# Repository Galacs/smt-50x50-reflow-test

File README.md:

# SMT 50x50 reflow test

ESP32-C6 50x50 board made to test smd reflow techniques with various components packages (QFN, HTSOP, WSON, USBC, SOT, SOIC, 0201)

## IC List

- ESP32-C6 (Main MCU)
- W25Q128JVSIQ (16MB program storage spi flash)
- 2x TMP117 (I2C temperature sensor)
- BMP581 (I2C/SPI pressure sensor)
- LMR36520 (wide Vin buck converter)
- LM317A (high Vin LDO)
- AP2112K (MCU LDO)
- 2450AT18A100E (2.45GHz Ceramic chip antenna)
- 01005 resistors

## Top preview

## Preview 3d render

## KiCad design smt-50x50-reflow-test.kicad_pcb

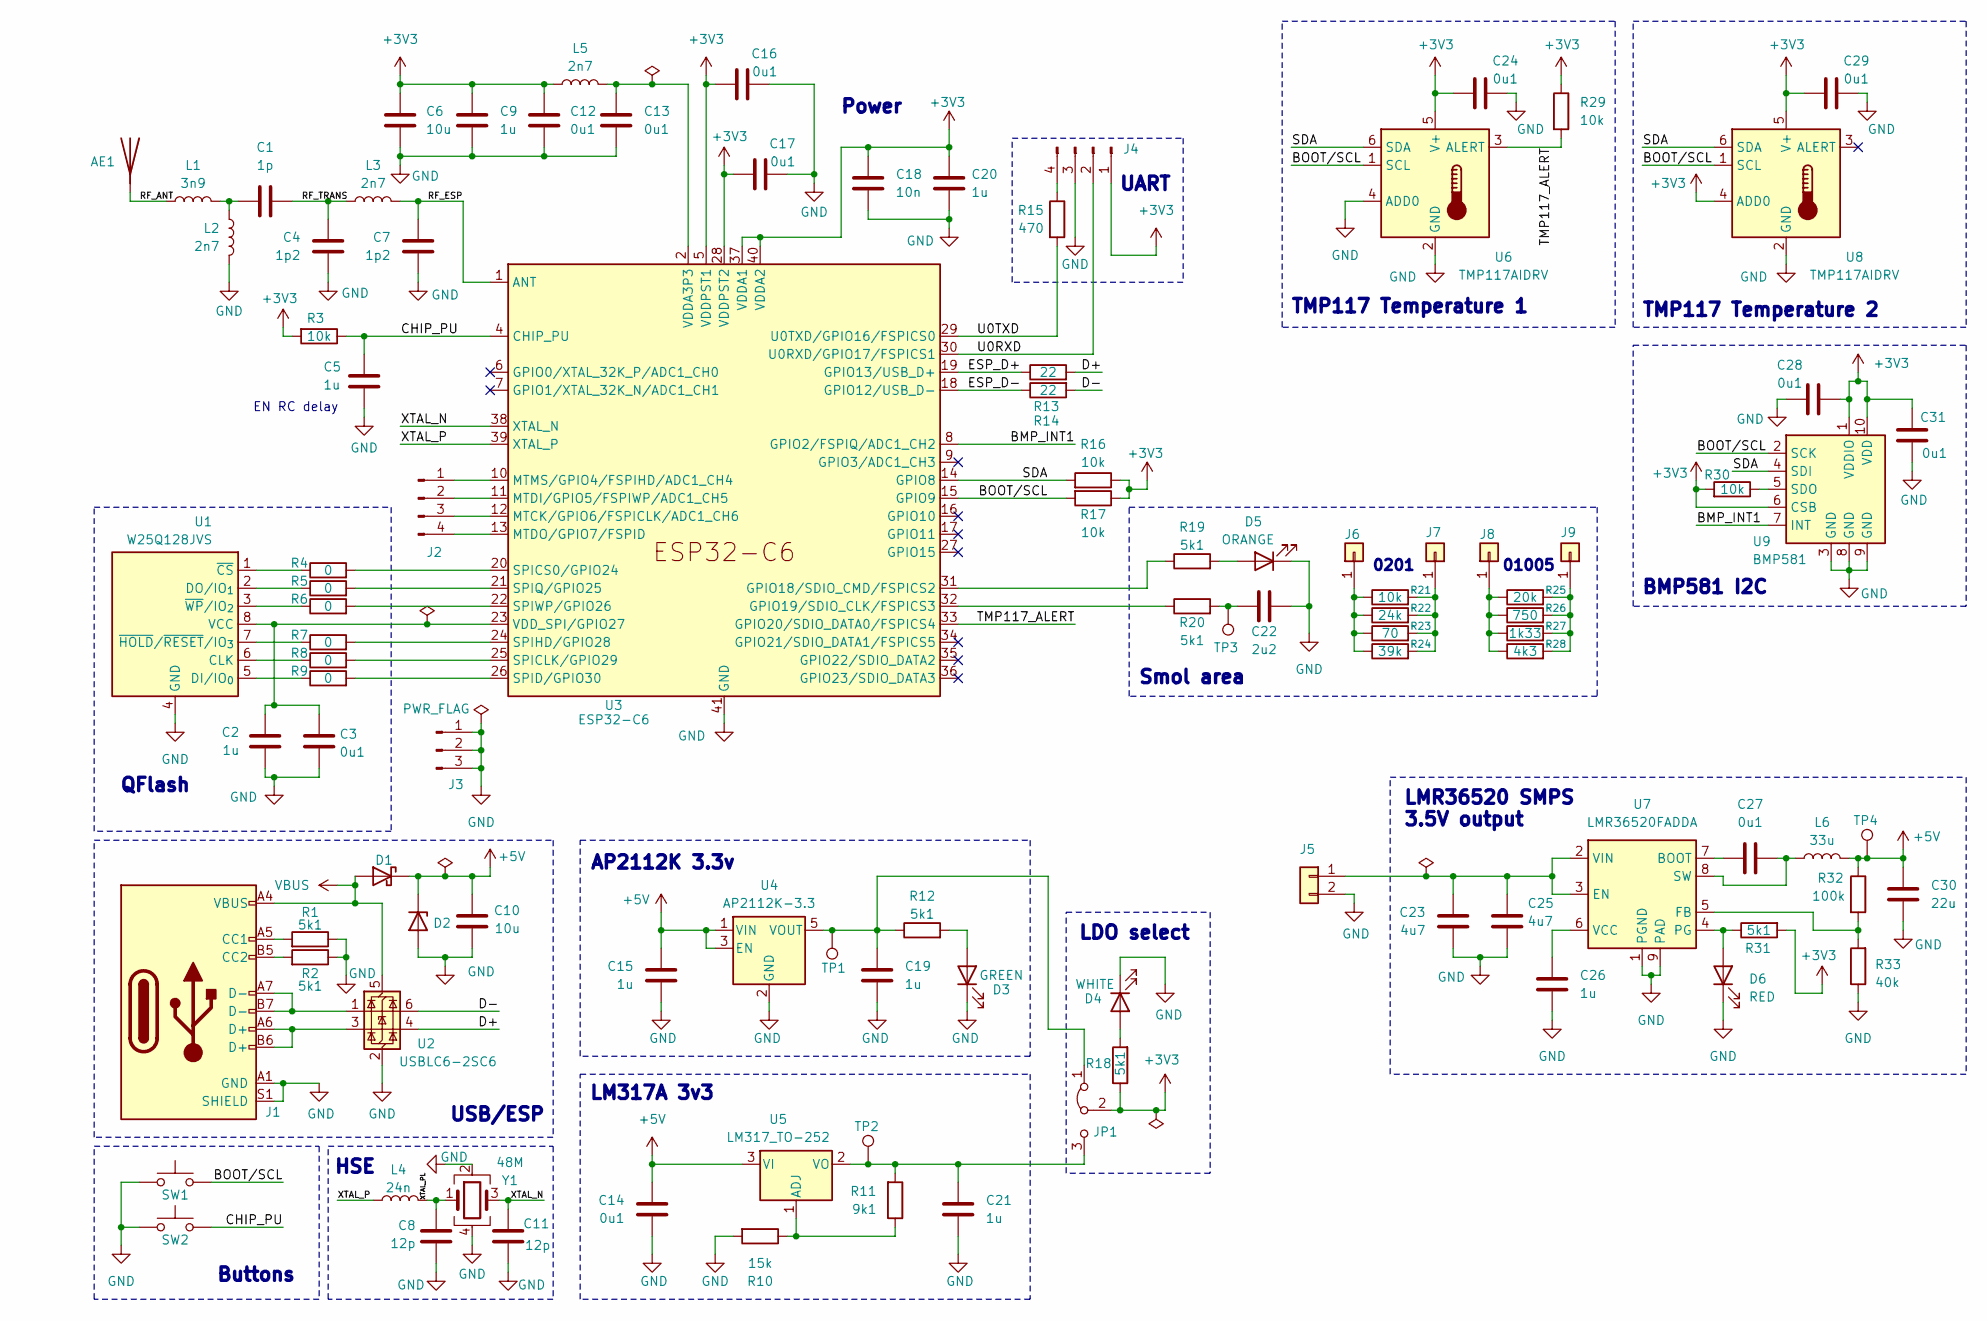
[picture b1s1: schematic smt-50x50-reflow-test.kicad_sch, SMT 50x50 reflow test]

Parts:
AE1: Antenna; Johanson_2450AT18x100; Manufacturer Part Number 2450AT18A100E; JLCPCB Part # C89334
C1: 1p; C_0402_1005Metric; Manufacturer Part Number 0402CG1R0C500NT; JLCPCB Part # C1550
C2, C5, C9, C20, C26: 1u; C_0402_1005Metric; Manufacturer Part Number CL05A105KA5NQNC; JLCPCB Part # C52923
C3, C12, C13, C16, C17, C24, C27, C28, C29, C31: 0u1; C_0402_1005Metric; Manufacturer Part Number CL05B104KB54PNC; JLCPCB Part # C307331
C4, C7: 1p2; C_0402_1005Metric; Manufacturer Part Number GJM1555C1H1R2WB01D; JLCPCB Part # C76899
C6, C10: 10u; C_0402_1005Metric; Manufacturer Part Number CL05A106MQ5NUNC; JLCPCB Part # C15525
C8, C11: 12p; C_0402_1005Metric; Manufacturer Part Number 0402CG120J500NT; JLCPCB Part # C1547
C14: 0u1; C_0603_1608Metric; Manufacturer Part Number CC0603KRX7R9BB104; JLCPCB Part # C14663
C15, C19, C21: 1u; C_0603_1608Metric; Manufacturer Part Number CL10A105KB8NNNC; JLCPCB Part # C15849
C18: 10n; C_0402_1005Metric; Manufacturer Part Number CL05B103KB5NNNC; JLCPCB Part # C15195
C22: 2u2; C_0201_0603Metric; Manufacturer Part Number GRM033R61A225KE47D; JLCPCB Part # C335106
C23, C25: 4u7; C_1206_3216Metric; Manufacturer Part Number 1206B475K500NT; JLCPCB Part # C29823
C30: 22u; C_0603_1608Metric; Manufacturer Part Number CL10A226MQ8NRNC; JLCPCB Part # C59461
D1: D_Schottky; D_SMA; Manufacturer Part Number SS54; JLCPCB Part # C22452
D2: H5VU10U; Diode_DFN1006; Manufacturer Part Number H5VU10U; JLCPCB Part # C22395519
D3: GREEN; LED_0805_2012Metric; Manufacturer Part Number KT-0805G; JLCPCB Part # C2297
D4: WHITE; LED_0603_1608Metric; Manufacturer Part Number KT-0603W; JLCPCB Part # C2290
D5: ORANGE; LED_0201_0603Metric; Manufacturer Part Number XL-0201UOC; JLCPCB Part # C5440629
D6: RED; LED_0603_1608Metric; Manufacturer Part Number KT-0603R; JLCPCB Part # C2286
J1: USB_C_Receptacle_USB2.0_14P; USB_C_Receptacle_HRO_TYPE-C-31-M-12; Manufacturer Part Number TYPE-C16PIN; JLCPCB Part # C393939
J2, J4: Conn_01x04_Pin; PinHeader_1x04_P2.54mm_Vertical
J3: Conn_01x03_Pin; PinHeader_1x03_P2.54mm_Vertical
J5: Conn_01x02; PinHeader_1x02_P2.54mm_Vertical
J6, J7, J8, J9: Conn_01x01; TestPoint_Pad_D1.0mm
JP1: Jumper_3_Bridged12; PinHeader_1x03_P2.54mm_Vertical
L1: 3n9; L_0402_1005Metric; Manufacturer Part Number LQG15HS3N9S02D; JLCPCB Part # C77109
L2, L3, L5: 2n7; L_0402_1005Metric; Manufacturer Part Number LQG15HS2N7S02D; JLCPCB Part # C77108
L4: 24n; L_0402_1005Metric; Manufacturer Part Number LQW15AN24NG00D; JLCPCB Part # C167472
L6: 33u; L_Chilisin_BMRx00060630; Manufacturer Part Number FXL0630-330-M; JLCPCB Part # C177245
R1, R2, R12, R18, R31: 5k1; R_0603_1608Metric; Manufacturer Part Number 0603WAF5101T5E; JLCPCB Part # C23186
R3, R29, R30: 10k; R_0603_1608Metric; Manufacturer Part Number 0603WAF1002T5E; JLCPCB Part # C25804
R4, R5, R6, R7, R8, R9: 0; R_0402_1005Metric; Manufacturer Part Number 0402WGF0000TCE; JLCPCB Part # C17168
R10: 15k; R_0603_1608Metric; Manufacturer Part Number 0603WAF1502T5E; JLCPCB Part # C22809
R11: 9k1; R_0603_1608Metric; Manufacturer Part Number 0603WAF9101T5E; JLCPCB Part # C23260
R13, R14: 22; R_0402_1005Metric; Manufacturer Part Number 0402WGF220JTCE; JLCPCB Part # C25092
R15: 470; R_0402_1005Metric; Manufacturer Part Number 0402WGF4700TCE; JLCPCB Part # C25117
R16, R17: 10k; R_0402_1005Metric; Manufacturer Part Number 0402WGF1002TCE; JLCPCB Part # C25744
R19, R20: 5k1; R_0201_0603Metric; Manufacturer Part Number 0201WMF5101TEE; JLCPCB Part # C270344
R21: 10k; R_0201_0603Metric; Manufacturer Part Number 0201WMF1002TEE C473048; JLCPCB Part # C473048
R22: 24k; R_0201_0603Metric; Manufacturer Part Number 0201WMF2402TEE; JLCPCB Part # C270353
R23: 70; R_0201_0603Metric; Manufacturer Part Number 0201WMF698JTEE; JLCPCB Part # C270692
R24: 39k; R_0201_0603Metric; Manufacturer Part Number 0201WMF3902TEE; JLCPCB Part # C473053
R25: 20k; R_01005_0402Metric; Manufacturer Part Number 0105WHJ0203TDE; JLCPCB Part # C560400
R26: 750; R_01005_0402Metric; Manufacturer Part Number RC0100FR-07750RL; JLCPCB Part # C850442
R27: 1k33; R_01005_0402Metric; Manufacturer Part Number MCR004QLPF1331; JLCPCB Part # C507485
R28: 4k3; R_01005_0402Metric; Manufacturer Part Number 0105WHF4301TDE; JLCPCB Part # C560366
R32: 100k; R_0603_1608Metric; Manufacturer Part Number 0603WAF1003T5E; JLCPCB Part # C25803
R33: 40k; R_0603_1608Metric; Manufacturer Part Number 0603WAF4022T5E; JLCPCB Part # C12447
SW1, SW2: SW_Push; SW_SPST_TS-1088-xR020; Manufacturer Part Number TS-1088-AR02016; JLCPCB Part # C720477
TP1, TP2, TP3, TP4: TestPoint; TestPoint_Pad_D2.0mm
U1: W25Q128JVS; SOIC-8_5.3x5.3mm_P1.27mm; Manufacturer Part Number W25Q128JVSIQ; JLCPCB Part # C97521
U2: USBLC6-2SC6; SOT-23-6; Manufacturer Part Number USBLC6-2SC6; JLCPCB Part # C7519
U3: ESP32-C6; QFN-40-1EP_5x5mm_P0.4mm_EP3.6x3.6mm_ThermalVias; Manufacturer Part Number ESP32-C6; JLCPCB Part # C5364646
U4: AP2112K-3.3; SOT-23-5; Manufacturer Part Number AP2112K-3.3TRG1; JLCPCB Part # C51118
U5: LM317_TO-252; TO-252-2; Manufacturer Part Number LM317AG-TN3-R; JLCPCB Part # C75510
U6, U8: TMP117AIDRV; WSON-6-1EP_2x2mm_P0.65mm_EP1x1.6mm; Manufacturer Part Number TMP117AIDRVR; JLCPCB Part # C699536
U7: LMR36520FADDA; Texas_HTSOP-8-1EP_3.9x4.9mm_P1.27mm_EP2.95x4.9mm_Mask2.4x3.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; Manufacturer Part Number LMR36520FADDAR; JLCPCB Part # C1858395
U9: BMP581; Bosch_LGA-10_2x2mm_P0.8mm_AntiClockwisePinNumbering; Manufacturer Part Number BMP581; JLCPCB Part # C5362283
Y1: 48M; Crystal_SMD_2016-4Pin_2.0x1.6mm; Manufacturer Part Number R940000096; JLCPCB Part # C7206306

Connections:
+3V3: C6.1, C9.1, C12.1, C16.1, C17.1, C18.1, C20.1, C24.1, C28.1, C29.1, C31.2, J4.1, JP1.2 (C), L5.1, R3.2, R16.1, R17.1, R18.1, R29.1, R30.2, R31.2, U3.5 (VDDPST1), U3.28 (VDDPST2), U3.37 (VDDA1), U3.40 (VDDA2), U6.5 (V+), U8.4 (ADD0), U8.5 (V+), U9.1 (VDDIO), U9.6 (CSB), U9.10 (VDD)
+5V: C10.1, C14.1, C15.1, C30.2, D1.1 (K), D2.1 (K), L6.2, R32.1, TP4.1, U4.1 (VIN), U4.3 (EN), U5.3 (VI)
/BMP_INT1: U3.8 (GPIO2/FSPIQ/ADC1_CH2), U9.7 (INT)
/BOOT/SCL: R17.2, SW1.2, U3.15 (GPIO9), U6.1 (SCL), U8.1 (SCL), U9.2 (SCK)
/CHIP_PU: C5.1, R3.1, SW2.2, U3.4 (CHIP_PU)
/D+: R13.2, U2.4 (I/O2)
/D-: R14.2, U2.6 (I/O1)
/ESP_D+: R13.1, U3.19 (GPIO13/USB_D+)
/ESP_D-: R14.1, U3.18 (GPIO12/USB_D-)
/RF_ANT: AE1.1 (A), L1.1
/RF_ESP: C7.1, L3.2, U3.1 (ANT)
/RF_TRANS: C1.1, C4.1, L3.1
/SDA: R16.2, U3.14 (GPIO8), U6.6 (SDA), U8.6 (SDA), U9.4 (SDI)
/TMP117_ALERT: R29.2, U3.33 (GPIO20/SDIO_DATA0/FSPICS4), U6.3 (ALERT)
/U0RXD: J4.2, U3.30 (U0RXD/GPIO17/FSPICS1)
/U0TXD: R15.2, U3.29 (U0TXD/GPIO16/FSPICS0)
/XTAL_N: C11.1, U3.38 (XTAL_N), Y1.3
/XTAL_P: L4.1, U3.39 (XTAL_P)
/XTAL_PL: C8.2, L4.2, Y1.1
GND: C2.2, C3.2, C4.2, C5.2, C6.2, C7.2, C8.1, C9.2, C10.2, C11.2, C12.2, C13.2, C14.2, C15.2, C16.2, C17.2, C18.2, C19.2, C20.2, C21.2, C22.2, C23.2, C24.2, C25.2, C26.2, C28.2, C29.2, C30.1, C31.1, D2.2 (A), D3.1 (K), D4.1 (K), D5.1 (K), D6.1 (K), J1.A1 (GND), J1.A12 (GND), J1.B1 (GND), J1.B12 (GND), J1.S1 (SHIELD), J3.1, J3.2, J3.3, J4.3, J5.2, L2.1, R1.1, R2.1, R10.2, R33.1, SW1.1, SW2.1, U1.4 (GND), U2.2 (GND), U3.41 (GND), U4.2 (GND), U6.2 (GND), U6.4 (ADD0), U7.1 (PGND), U7.9 (PAD), U8.2 (GND), U9.3 (GND), U9.8 (GND), U9.9 (GND), Y1.2, Y1.4
unnamed: C1.2, L1.2, L2.2
unnamed: C13.1, L5.2, U3.2 (VDDA3P3), U3.3 (VDDA3P3)
unnamed: C22.1, R20.2, TP3.1
unnamed: D3.2 (A), R12.2
unnamed: D4.2 (A), R18.2
unnamed: D5.2 (A), R19.2
unnamed: D6.2 (A), R31.1, U7.4 (PG)
unnamed: J1.A5 (CC1), R1.2
unnamed: J1.B5 (CC2), R2.2
unnamed: J1.A6 (D+), J1.B6 (D+), U2.3 (I/O2)
unnamed: J1.A7 (D-), J1.B7 (D-), U2.1 (I/O1)
unnamed: J2.1, U3.10 (MTMS/GPIO4/FSPIHD/ADC1_CH4)
unnamed: J2.2, U3.11 (MTDI/GPIO5/FSPIWP/ADC1_CH5)
unnamed: J2.3, U3.12 (MTCK/GPIO6/FSPICLK/ADC1_CH6)
unnamed: J2.4, U3.13 (MTDO/GPIO7/FSPID)
unnamed: J4.4, R15.1
unnamed: C23.1, C25.1, J5.1, U7.2 (VIN), U7.3 (EN)
unnamed: J6.1, R21.1, R22.1, R23.1, R24.1
unnamed: J7.1, R21.2, R22.2, R23.2, R24.2
unnamed: J8.1, R25.1, R26.1, R27.1, R28.1
unnamed: J9.1, R25.2, R26.2, R27.2, R28.2
unnamed: C19.1, JP1.1 (A), R12.1, TP1.1, U4.5 (VOUT)
unnamed: C21.1, JP1.3 (B), R11.2, TP2.1, U5.2 (VO)
unnamed: R8.1, U1.6 (CLK)
unnamed: R9.1, U1.5 (DI/IO_{0})
unnamed: R5.1, U1.2 (DO/IO_{1})
unnamed: C2.1, C3.1, U1.8 (VCC), U3.23 (VDD_SPI/GPIO27)
unnamed: R4.1, U1.1 (~CS)
unnamed: R7.1, U1.7 (~HOLD/~RESET/IO_{3})
unnamed: R6.1, U1.3 (~WP/IO_{2})
unnamed: R19.1, U3.31 (GPIO18/SDIO_CMD/FSPICS2)
unnamed: R20.1, U3.32 (GPIO19/SDIO_CLK/FSPICS3)
unnamed: R8.2, U3.25 (SPICLK/GPIO29)
unnamed: R4.2, U3.20 (SPICS0/GPIO24)
unnamed: R9.2, U3.26 (SPID/GPIO30)
unnamed: R7.2, U3.24 (SPIHD/GPIO28)
unnamed: R5.2, U3.21 (SPIQ/GPIO25)
unnamed: R6.2, U3.22 (SPIWP/GPIO26)
unnamed: R10.1, R11.1, U5.1 (ADJ)
unnamed: C27.2, U7.7 (BOOT)
unnamed: R32.2, R33.2, U7.5 (FB)
unnamed: C27.1, L6.1, U7.8 (SW)
unnamed: C26.1, U7.6 (VCC)
unnamed: R30.1, U9.5 (SDO)
VBUS: D1.2 (A), J1.A4 (VBUS), J1.A9 (VBUS), J1.B4 (VBUS), J1.B9 (VBUS), U2.5 (VBUS)

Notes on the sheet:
TMP117 Temperature 2
0201
UART
Smol area
HSE
LM317A 3v3
Buttons
AP2112K 3.3v
EN RC delay
BMP581 I2C
TMP117 Temperature 1
USB/ESP
Power
LMR36520 SMPS 3.5V output
01005
LDO select
QFlash

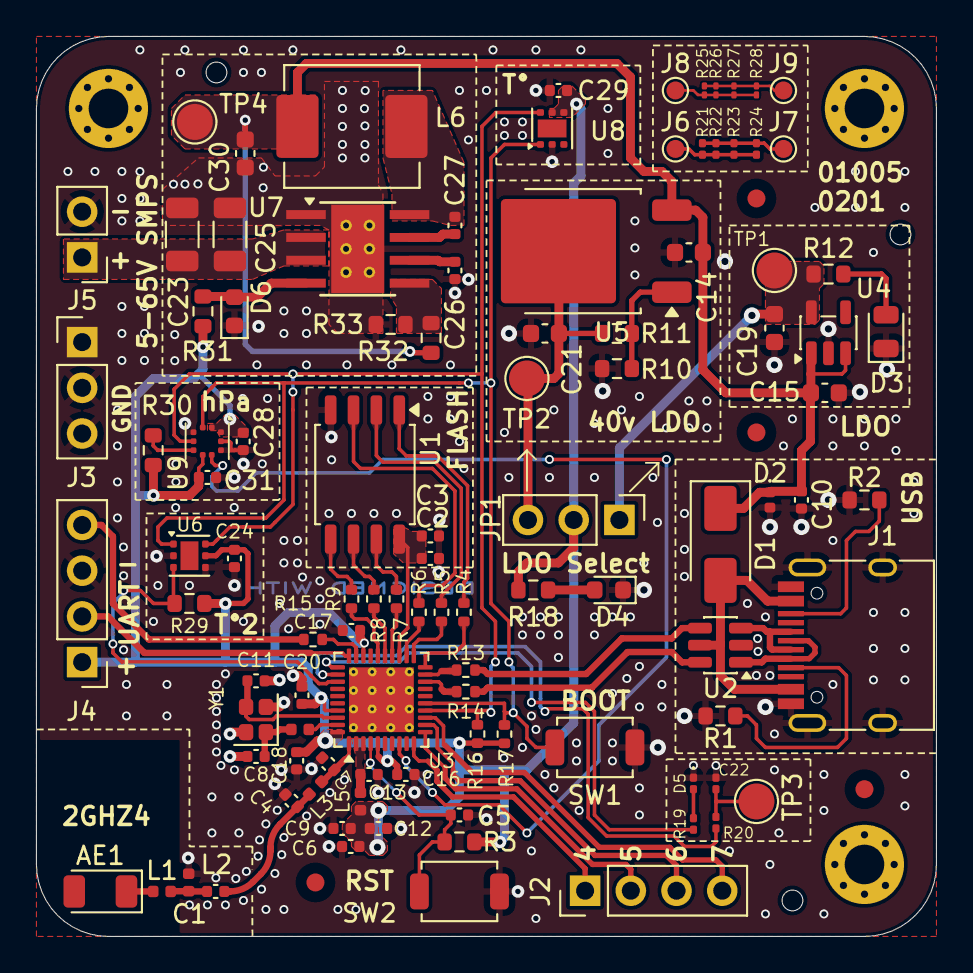
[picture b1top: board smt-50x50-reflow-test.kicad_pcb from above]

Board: 4 copper layers, 50.0 x 50.0 mm, 103 parts (0 on the bottom side), 65 nets.

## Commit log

2025-11-15 schem: import esp32-c6, uart, usb-c, flash, crystal, buttons, tmp117, bmp581 from esp32c6-sensor-devboard
2025-11-15 schem: add LM317A 3v3 ldo
2025-11-15 schem: import AP2112K 3.3v ldo from esp32c6-sensor-devboard
2025-11-15 schem: import ldo select from esp32s3-poc-devboard
2025-11-15 schem: import LMR36520 3.5v smps from esp32c6-sensor-devboard
2025-11-15 schem: add no connects
2025-11-15 schem: import net classes
2025-11-15 schem: add missing i2c net labels
2025-11-15 schem: add missing footprints
2025-11-15 schem: add ordering info to BOM
2025-11-15 schem: add title
2025-11-15 schem: add esd protection to usb vbus
2025-11-15 pcb: import stackup
2025-11-15 pcb: fix missing 3d models
2025-11-15 pcb: add board outline
2025-11-15 pcb: add M2 mounting holes
2025-11-15 pcb: add M2 tooling holes
2025-11-15 pcb: add fiducials
2025-11-15 pcb: initial rough placement
2025-11-15 schem: run and fix ERC
2025-11-15 pcb: placement refinement
2025-11-15 schem: add smol area
2025-11-16 pcb: refine rf layout
2025-11-16 pcb: align headers on a 2.54mm grid
2025-11-16 pcb: add usb routing
2025-11-16 pcb: add internal gnd planes
2025-11-16 pcb: add stiching vias
2025-11-16 pcb: add rf routing
2025-11-16 pcb: add crystal routing
2025-11-16 pcb: add SPI FLASH routing
2025-11-16 pcb: add SMPS routing
2025-11-16 pcb: add 3v3 routing
2025-11-16 pcb: import smol area from schem
2025-11-16 pcb: add smol area layout
2025-11-16 pcb: add smol area routing
2025-11-16 pcb: add missing 3v3 routing
2025-11-16 pcb: add 5v routing
2025-11-16 pcb: add power section routing
2025-11-16 pcb: add i2c routing
2025-11-16 pcb: add spare gpio routing
2025-11-16 pcb: route CHIP_PU
2025-11-16 schem: remove one TMP117 alert line
2025-11-16 pcb: route TMP117 and BMP581 interrupts
2025-11-16 pcb(silkscreen): clean up reference designators
2025-11-16 pcb: add top and bottom gnd planes
2025-11-16 pcb: add stitching vias
2025-11-16 schem: run and fix DRC
2025-11-16 pcb: remove unused internal pads
2025-11-16 pcb(silkscreen): add user info
2025-11-16 pcb: finish silkscreen
2025-11-16 pcb: add title
2025-11-16 schem: add missing BOM info
2025-11-16 pcb: add production files
2025-11-26 fix silkscreen and regenerate production files
2025-11-26 pcb: replace 何何 placeholder
2025-11-30 add README.md
2025-11-30 add images to readme
2025-11-30 fix README title
